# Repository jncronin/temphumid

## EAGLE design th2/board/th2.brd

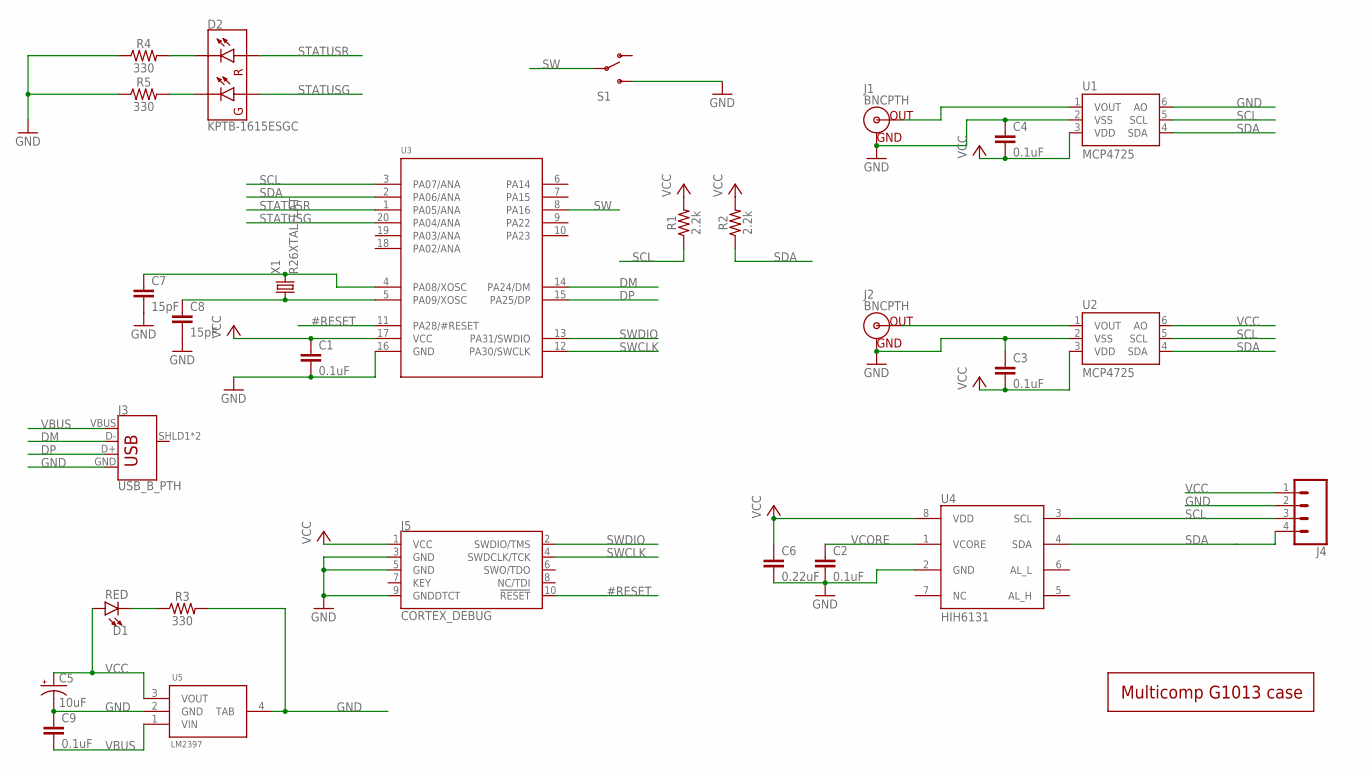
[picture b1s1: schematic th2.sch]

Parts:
C1, C2, C3, C4, C9: 0.1uF; 0603
C5: 10uF; CPOL-RADIAL-2.5MM-5MM
C6: 0.22uF; 0603
C7, C8: 15pF; 0603
D1: RED; LED-0603
D2: KPTB-1615ESGC; LTST-C195KGJRKT
J1, J2: BNCPTH; BNC
J3: USB_B_PTH; USB-B-PTH
J4: CONN_041.27MM; 1X04_1.27MM
J5: CORTEX_DEBUG; SAMTECH_FTSH-105-01
R1, R2: 2.2k; 0603
R3, R4, R5: 330; 0603
S1: SWITCH-SPDTSMD; SWITCH_SPDT_SMD
U1, U2: MCP4725; SOT23-6
U3: SAMD11D14A; SOIC20L
U4: HIH6131; SOIC8
U5: LM2397; SOT223
U$1: G1013HOLES
X1: R26XTALFLAT; R26FLAT

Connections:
#RESET: J5.10 (!RESET), U3.11 (PA28/#RESET)
DM: J3.D-, U3.14 (PA24/DM)
DP: J3.D+, U3.15 (PA25/DP)
GND: C1.2, C2.2, C3.1, C4.1, C5.2 (-), C6.2, C7.2, C8.2, C9.1, J1.GND, J2.GND, J3.GND, J4.2, J5.3 (GND), J5.5 (GND), J5.9 (GNDDTCT), R3.2, R4.1, R5.1, S1.3 (S), U1.2 (VSS), U1.6 (AO), U2.2 (VSS), U3.16 (GND), U4.2 (GND), U5.2 (GND), U5.4 (TAB)
unnamed: C7.1, U3.4 (PA08/XOSC), X1.P$2 (2)
unnamed: C8.1, U3.5 (PA09/XOSC), X1.P$1 (1)
unnamed: D1.C, R3.1
unnamed: D2.P$4 (RC), R4.2
unnamed: D2.P$3 (GC), R5.2
unnamed: J1.S (OUT), U1.1 (VOUT)
unnamed: J2.S (OUT), U2.1 (VOUT)
SCL: J4.3, R1.1, U1.5 (SCL), U2.5 (SCL), U3.3 (PA07/ANA), U4.3 (SCL)
SDA: J4.4, R2.1, U1.4 (SDA), U2.4 (SDA), U3.2 (PA06/ANA), U4.4 (SDA)
STATUSG: D2.P$1 (GA), U3.20 (PA04/ANA)
STATUSR: D2.P$2 (RA), U3.1 (PA05/ANA)
SW: S1.2, U3.8 (PA16)
SWCLK: J5.4 (SWDCLK/TCK), U3.12 (PA30/SWCLK)
SWDIO: J5.2 (SWDIO/TMS), U3.13 (PA31/SWDIO)
VBUS: C9.2, J3.VBUS, U5.1 (VIN)
VCC: C1.1, C3.2, C4.2, C5.1 (+), C6.1, D1.A, J4.1, J5.1 (VCC), R1.2, R2.2, U1.3 (VDD), U2.3 (VDD), U2.6 (AO), U3.17 (VCC), U4.8 (VDD), U5.3 (VOUT)
VCORE: C2.1, U4.1 (VCORE)

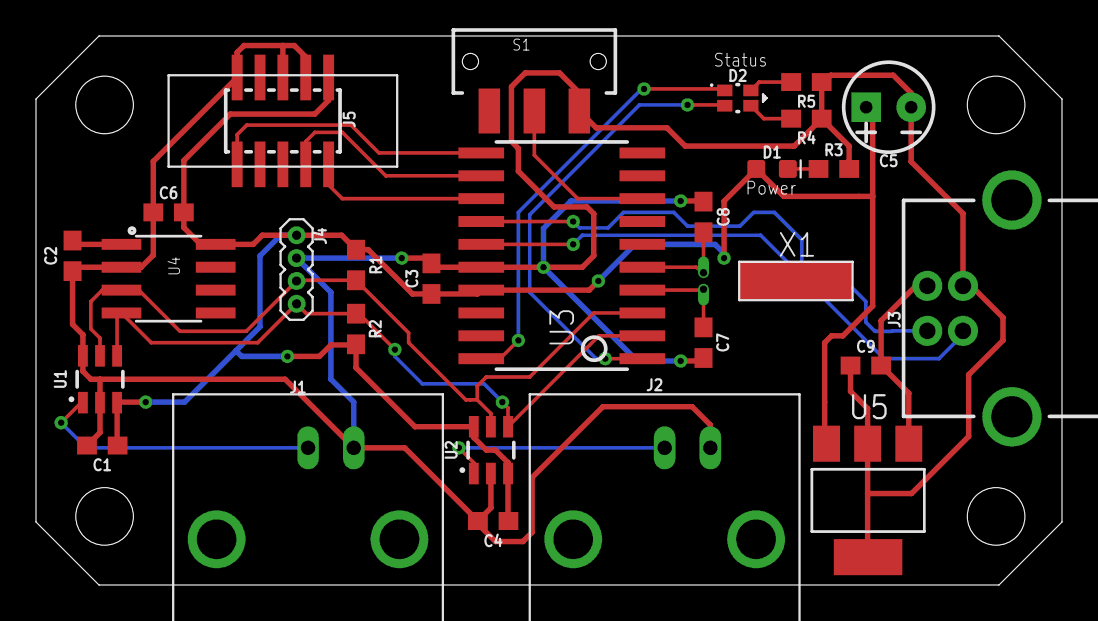
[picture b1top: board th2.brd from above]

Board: 2 copper layers, 57.0 x 30.5 mm, 29 parts (0 on the bottom side), 21 nets.

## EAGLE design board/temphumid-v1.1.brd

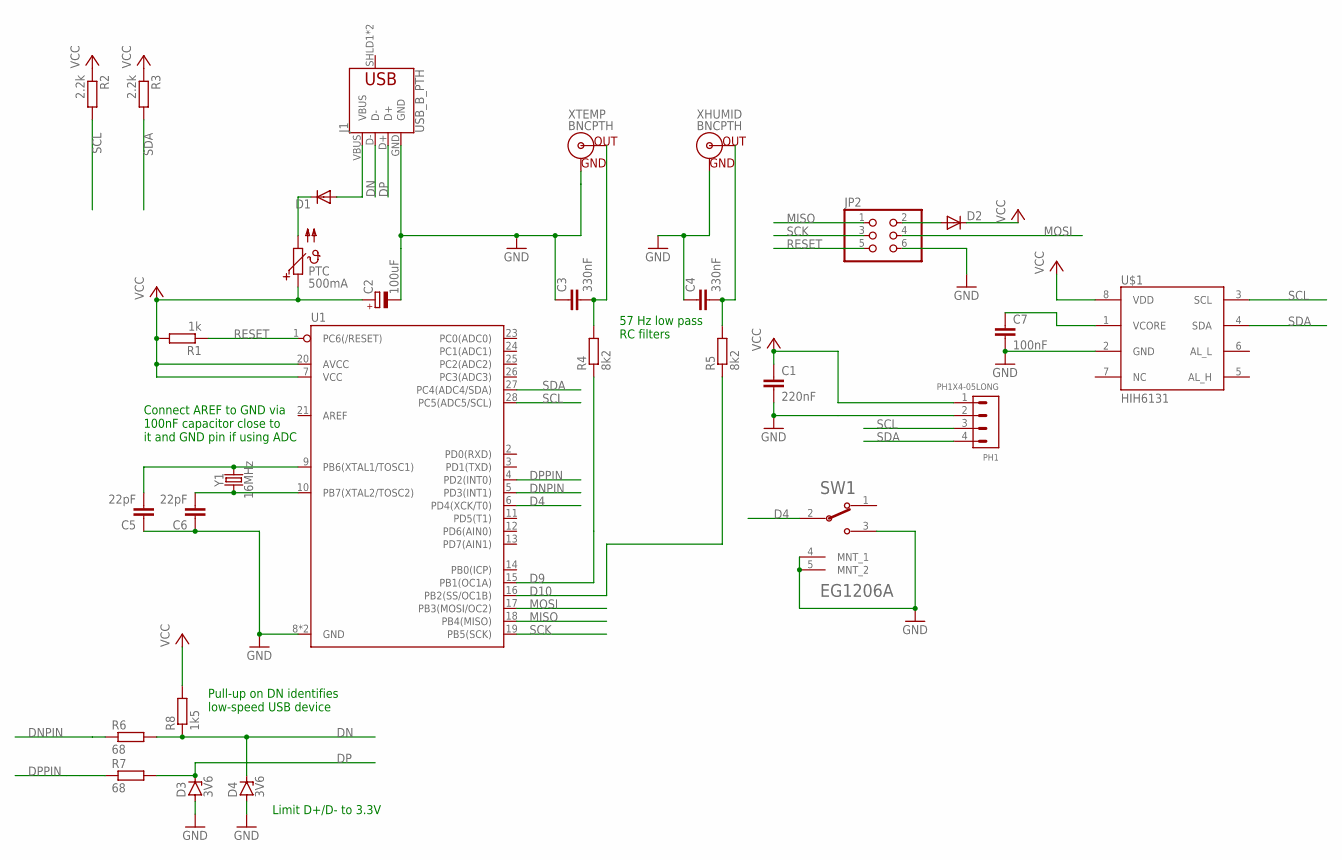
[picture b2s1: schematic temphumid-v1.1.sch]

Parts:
C1: 220nF; C025-024X044
C2: 100uF; E2,5-6E
C3, C4: 330nF; C025-024X044
C5, C6: 22pF; C025-024X044
C7: 100nF; C025-024X044
D1, D2: 1N4004; DO41-10
D3, D4: 3V6; DO35Z10
J1: USB_B_PTH; USB-B-PTH
JP2: PINHD-2X3; 2X03
PH1: PH1X4-05LONG; PHL005-1-4
PTC: 500mA; P679
R1: 1k; 0207/7
R2, R3: 2.2k; 0207/7
R4, R5: 8k2; 0207/12
R6, R7: 68; 0204/7
R8: 1k5; 0204/7
SW1: E-SWITCH_EG1206AE-SWITCH_EG1206A_0_0; E-SWITCH_EG1206A_0
U1: ATMEGA328P_PDIP; DIP28
U$1: HIH6131; SOIC8
XHUMID: BNCPTH; BNC
XTEMP: BNCPTH; BNC
Y1: 16MHz; HC49US

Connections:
D4: SW1.2 (COM), U1.6 (PD4(XCK/T0))
D9: R4.1, U1.15 (PB1(OC1A))
D9OUT: C3.2, R4.2, XTEMP.S (OUT)
D10: R5.1, U1.16 (PB2(SS/OC1B))
D10OUT: C4.2, R5.2, XHUMID.S (OUT)
DN: D4.C, J1.D-, R6.2, R8.1
DNPIN: R6.1, U1.5 (PD3(INT1))
DP: D3.C, J1.D+, R7.2
DPPIN: R7.1, U1.4 (PD2(INT0))
GND: C1.2, C2.-, C3.1, C4.1, C5.1, C6.1, C7.2, D3.A, D4.A, J1.GND, JP2.6, PH1.2, SW1.3, SW1.4 (MNT_1), SW1.5 (MNT_2), U1.8 (GND), U1.22 (GND), U$1.2 (GND), XHUMID.GND, XTEMP.GND
MISO: JP2.1, U1.18 (PB4(MISO))
MOSI: JP2.4, U1.17 (PB3(MOSI/OC2))
unnamed: D1.C, PTC.2
unnamed: D1.A, J1.VBUS
unnamed: D2.A, JP2.2
unnamed: C5.2, U1.9 (PB6(XTAL1/TOSC1)), Y1.2
unnamed: C6.2, U1.10 (PB7(XTAL2/TOSC2)), Y1.1
unnamed: C7.1, U$1.1 (VCORE)
RESET: JP2.5, R1.1, U1.1 (PC6(/RESET))
SCK: JP2.3, U1.19 (PB5(SCK))
SCL: PH1.3, R2.2, U1.28 (PC5(ADC5/SCL)), U$1.3 (SCL)
SDA: PH1.4, R3.2, U1.27 (PC4(ADC4/SDA)), U$1.4 (SDA)
VCC: C1.1, C2.+, D2.C, PH1.1, PTC.1, R1.2, R2.1, R3.1, R8.2, U1.7 (VCC), U1.20 (AVCC), U$1.8 (VDD)

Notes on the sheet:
Connect AREF to GND via 100nF capacitor close to it and GND pin if using ADC
57 Hz low pass RC filters
Pull-up on DN identifies low-speed USB device
Limit D+/D- to 3.3V

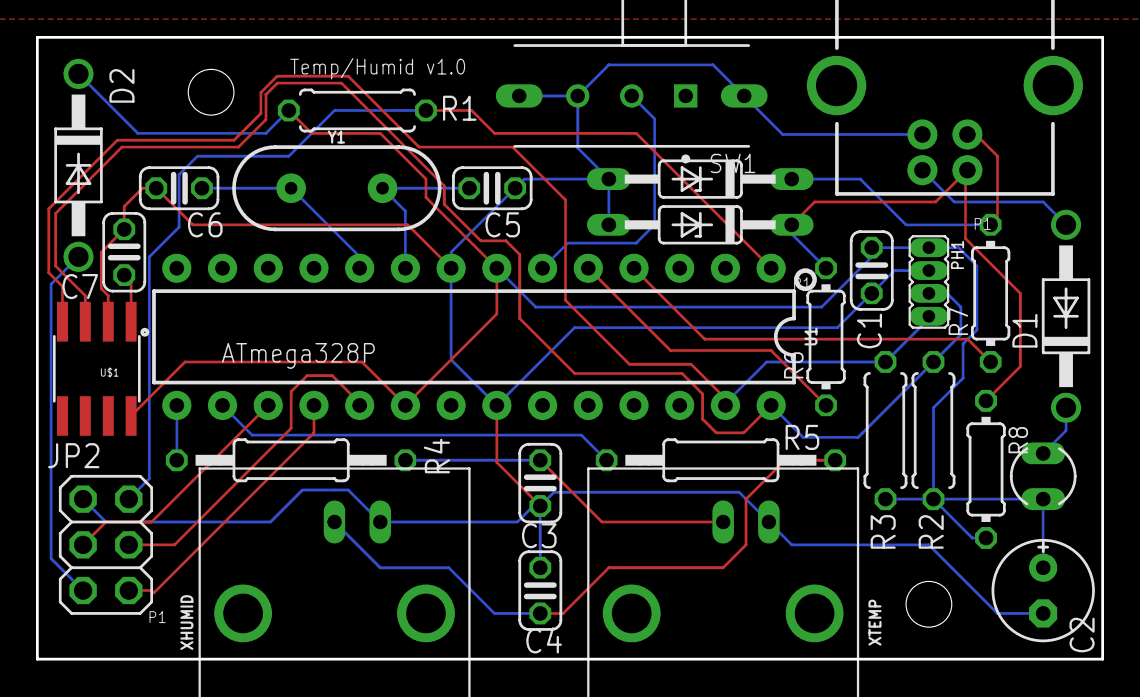
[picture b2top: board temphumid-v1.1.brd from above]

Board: 2 copper layers, 59.2 x 34.5 mm, 29 parts (0 on the bottom side), 23 nets.

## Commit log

2018-11-17 Do intermediate calculations with 0.01 accuracy to prevent loss of precision
2018-11-17 VSCode updates
2018-11-17 Rename usb variables
2018-11-18 Add VUSB USB driver and implement simple Control out message combining current temp and humid
2018-11-18 Add Win32 command line utility to read temp/humid over USB
2018-11-18 Add schematics
2018-11-19 Handle multiple devices
2018-11-19 Fix bug in multi-device code
2018-11-19 Update sensor values even if square wave switch is depressed (so USB output is still valid)
2018-11-20 Add library, .net wrapper and windows forms gui
2018-11-20 Change to use HID reports (1=temp, 2=humid)
2018-11-23 Add hotplug detection to gui app
2018-11-23 Upgrade board to v1.1 with new BNC connector
2019-02-02 Automatically save to disk Add random value generator if no device in debug mode for testing purposes
2019-03-17 Add support for th v2
2019-03-18 Add temphumid v2

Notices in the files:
parts and their libraries:
SparkFun-Connectors: Licensing: Creative Commons ShareAlike 4.0 International - https://creativecommons.org/licenses/by-sa/4.0
